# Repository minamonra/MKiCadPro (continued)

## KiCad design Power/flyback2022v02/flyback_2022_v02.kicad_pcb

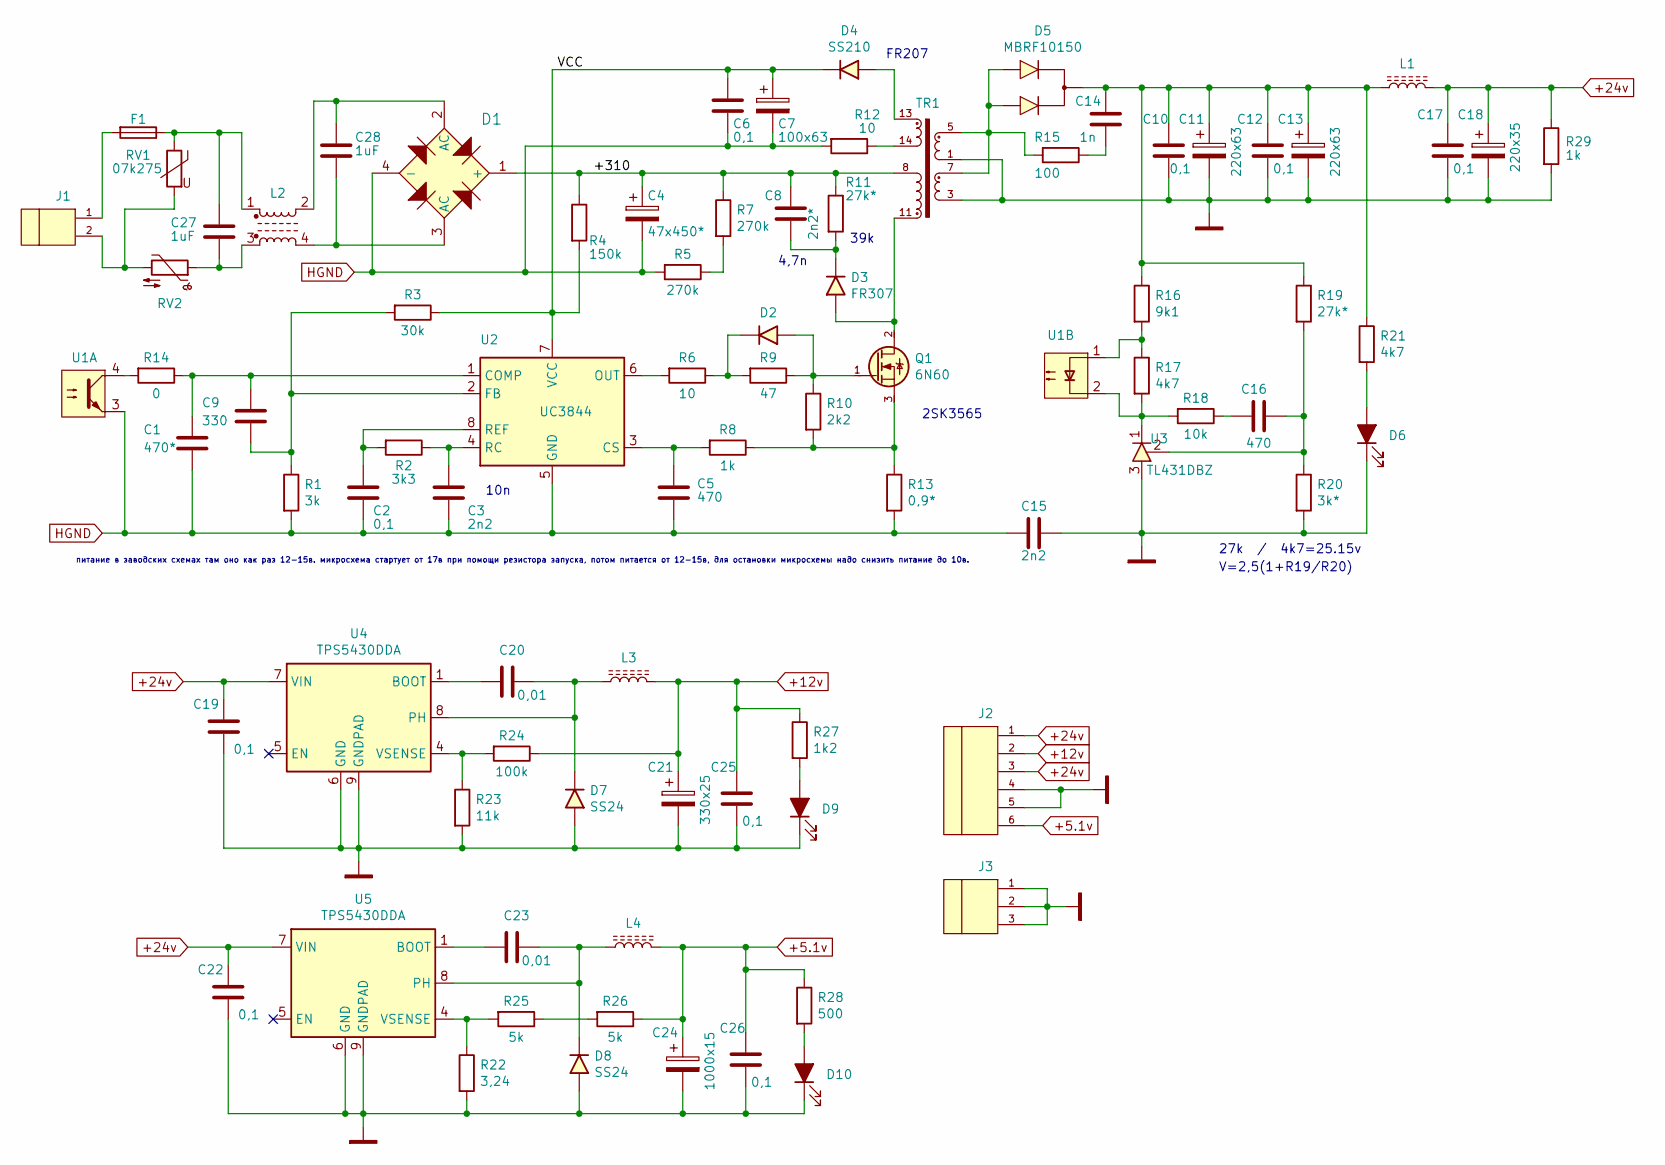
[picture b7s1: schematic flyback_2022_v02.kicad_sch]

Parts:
C1: 470*; capacitor_1206_3216Metric_V1
C2, C6, C10, C12, C17, C19, C22, C25, C26: 0,1; capacitor_1206_3216Metric_V1
C3: 2n2; capacitor_1206_3216Metric_V1
C4: 47x450*; CP_Radial_D17.0mm_P7.50mm
C5, C16: 470; capacitor_1206_3216Metric_V1
C7: 100x63; CP_D7.5_P2.5_zm0
C8: 2n2*; Capacitor_Y
C9: 330; capacitor_1206_3216Metric_V1
C11, C13: 220x63; CP_D10_P5.0_zm0
C14: 1n; capacitor_1206_3216Metric_V1
C15: 2n2; Capacitor_Y
C18: 220x35; CP_D10_P5.0_zm0
C20, C23: 0,01; capacitor_1206_3216Metric_V1
C21: 330x25; CP_D10_P5.0_zm0
C24: 1000x15; CP_D10_P5.0_zm0
C27, C28: 1uF; C_Rect_L10.0mm_W4.0mm_P7.50mm_MKS4
D1: KBP04G; Diode_bridge_RS207
D2: 4148; D_1206_3216Metric_Pad1.42x1.75mm_HandSolder
D3: FR307; D_DO-201AE_P5.08mm_Vertical_AnodeUp
D4: SS210; D_2010_5025Metric_SS14
D5: MBRF10150; HS_207_30_TO220
D6, D9, D10: LED_D3.0mm_zmod
D7, D8: SS24; D_2010_5025Metric_SS14
F1: 0,5; Fuseholder_BLX-A
J1: connector2p_v1; TerminalBlock_5_08_1
J2: connector6p; pin_1x06_P2.54mm_vertical
J3: connector3p; pin_1x03_P2.54mm_vertical
L1, L3, L4: L_Abracon_ASPI-0630LR
L2: Choke_Common_UU9LF
Q1: 6N60; HS_207_30_TO220
R1: 3k; resistor_1206_3216metric_V1
R2: 3k3; resistor_1206_3216metric_V1
R3: 30k; resistor_1206_3216metric_V1
R4: 150k; R_Axial_DIN0207_L6.3mm_D2.5mm_P10.16mm_Horizontal
R5, R7: 270k; resistor_1206_3216metric_V1
R6: 10; R_Axial_DIN0207_L6.3mm_D2.5mm_P10.16mm_Horizontal
R8: 1k; resistor_1206_3216metric_V1
R9: 47; resistor_1206_3216metric_V1
R10: 2k2; resistor_1206_3216metric_V1
R11: 27k*; R_Axial_DIN0614_L14.3mm_D5.7mm_P5.08mm_Vertical
R12: 10; resistor_1206_3216metric_V1
R13: 0,9*; R_Axial_DIN0207_L6.3mm_D2.5mm_P10.16mm_Horizontal
R14: 0; R_Axial_DIN0207_L6.3mm_D2.5mm_P10.16mm_Horizontal
R15: 100; R_Axial_DIN0614_L14.3mm_D5.7mm_P5.08mm_Vertical
R16: 9k1; resistor_1206_3216metric_V1
R17: 4k7; resistor_1206_3216metric_V1
R18: 10k; resistor_1206_3216metric_V1
R19: 27k*; resistor_1206_3216metric_V1
R20: 3k*; resistor_1206_3216metric_V1
R21: 4k7; R_Axial_DIN0207_L6.3mm_D2.5mm_P10.16mm_Horizontal
R22: 3,24; resistor_1206_3216metric_V1
R23: 11k; resistor_1206_3216metric_V1
R24: 100k; resistor_1206_3216metric_V1
R25, R26: 5k; resistor_1206_3216metric_V1
R27: 1k2; R_Axial_DIN0207_L6.3mm_D2.5mm_P10.16mm_Horizontal
R28: 500; resistor_1206_3216metric_V1
R29: 1k; R_Axial_DIN0614_L14.3mm_D5.7mm_P5.08mm_Vertical
RV1: 07k275; Capacitor_Y
RV2: 10; NTC_Thermistor_Epcos
TR1: Transformer_ETD29_1; Transformer_ETD-29_13_11_Horizontal
U1: PC817_AB; DIP-4_W7.62mm
U2: UC3844; DIP-8_W7.62mm_LongPads_3FLAT
U3: TL431DBZ; SOT-23
U4, U5: TPS5430DDA; TI_SO-PowerPAD-8_ThermalVias

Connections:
+5.1v: C24.1, C26.1, J2.6, L4.2, R26.1, R28.1
+12v: C21.1, C25.1, J2.2, L3.2, R24.1, R27.1
+24v: C17.1, C18.1, C19.1, C22.1, J2.1, J2.3, L1.2, R29.1, U4.7 (VIN), U5.7 (VIN)
/+310: C4.1, C8.1, D1.1 (+), R4.1, R7.1, R11.1, TR1.8
/VCC: C6.1, C7.1, D4.1 (K), R3.1, R4.2, U2.7 (VCC)
GND: C10.2, C11.2, C12.2, C13.2, C15.1, C17.2, C18.2, C19.2, C21.2, C22.2, C24.2, C25.2, C26.2, D6.1 (K), D7.2 (A), D8.2 (A), D9.1 (K), D10.1 (K), J2.4, J2.5, J3.1, J3.2, J3.3, R20.2, R22.2, R23.2, R29.2, TR1.1, TR1.3, U3.3 (A), U4.6 (GND), U4.9 (GNDPAD), U5.6 (GND), U5.9 (GNDPAD)
HGND: C1.2, C2.2, C3.2, C4.2, C5.2, C6.2, C7.2, C15.2, D1.4 (-), R1.2, R5.2, R12.2, R13.2, U1.3, U2.5 (GND)
unnamed: C1.1, C9.1, R14.1, U2.1 (COMP)
unnamed: C2.1, R2.2, U2.8 (REF)
unnamed: C3.1, R2.1, U2.4 (RC)
unnamed: C5.1, R8.2, U2.3 (CS)
unnamed: C8.2, D3.1 (K), R11.2
unnamed: C9.2, R1.1, R3.2, U2.2 (FB)
unnamed: C10.1, C11.1, C12.1, C13.1, C14.1, D5.2 (K), L1.1, R16.1, R19.1, R21.1
unnamed: C14.2, R15.1
unnamed: C16.1, R18.1
unnamed: C16.2, R19.2, R20.1, U3.2 (REF)
unnamed: C20.1, D7.1 (K), L3.1, U4.8 (PH)
unnamed: C20.2, U4.1 (BOOT)
unnamed: C23.1, D8.1 (K), L4.1, U5.8 (PH)
unnamed: C23.2, U5.1 (BOOT)
unnamed: C27.1, F1.1, L2.1, RV1.1
unnamed: C27.2, L2.3, RV2.1
unnamed: C28.1, D1.2 (AC), L2.2
unnamed: C28.2, D1.3 (AC), L2.4
unnamed: D2.1 (K), R6.1, R9.2
unnamed: D2.2 (A), Q1.1 (G), R9.1, R10.1
unnamed: D3.2 (A), Q1.2 (D), TR1.11
unnamed: D4.2 (A), TR1.13
unnamed: D5.1 (A), D5.3 (A), R15.2, TR1.5, TR1.7
unnamed: D6.2 (A), R21.2
unnamed: D9.2 (A), R27.2
unnamed: D10.2 (A), R28.2
unnamed: F1.2, J1.1
unnamed: J1.2, RV1.2, RV2.2
unnamed: Q1.3 (S), R8.1, R10.2, R13.1
unnamed: R5.1, R7.2
unnamed: R6.2, U2.6 (OUT)
unnamed: R12.1, TR1.14
unnamed: R14.2, U1.4
unnamed: R16.2, R17.1, U1.1
unnamed: R17.2, R18.2, U1.2, U3.1 (K)
unnamed: R22.1, R25.2, U5.4 (VSENSE)
unnamed: R23.1, R24.2, U4.4 (VSENSE)
unnamed: R25.1, R26.2

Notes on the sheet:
V=2,5(1+R19/R20)
39k
FR207
4,7n
питание в заводских схемах там оно как раз 12-15в. микросхема стартует от 17в при помощи резистора запуска, потом питается от 12-15в, для остановки микросхемы надо снизить питание до 10в.
27k / 4k7=25.15v
2SK3565
10n

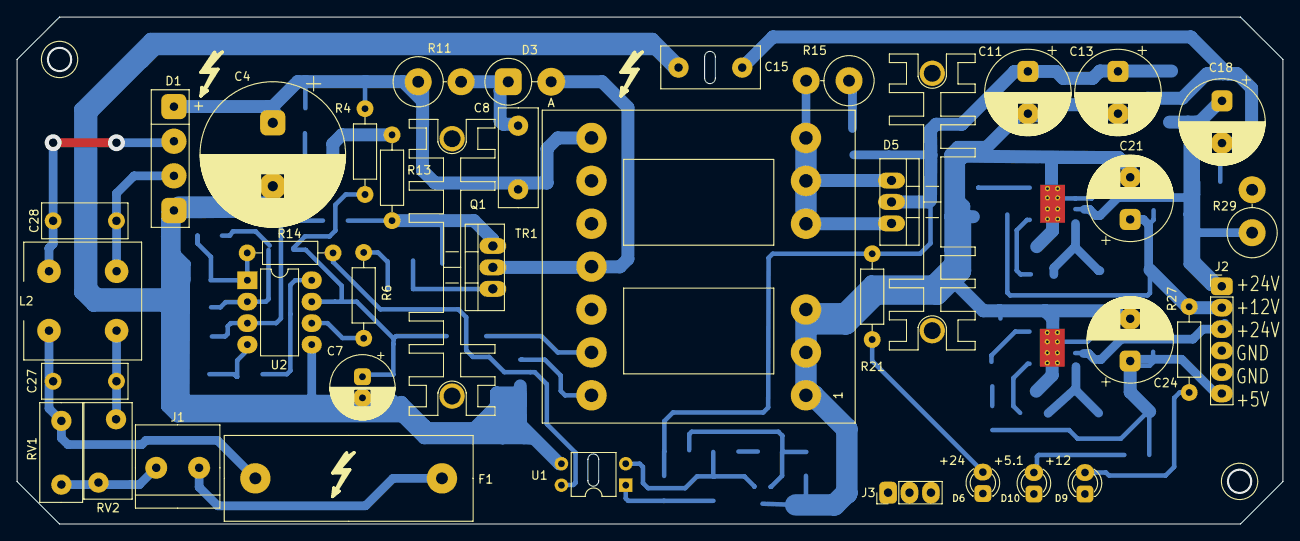
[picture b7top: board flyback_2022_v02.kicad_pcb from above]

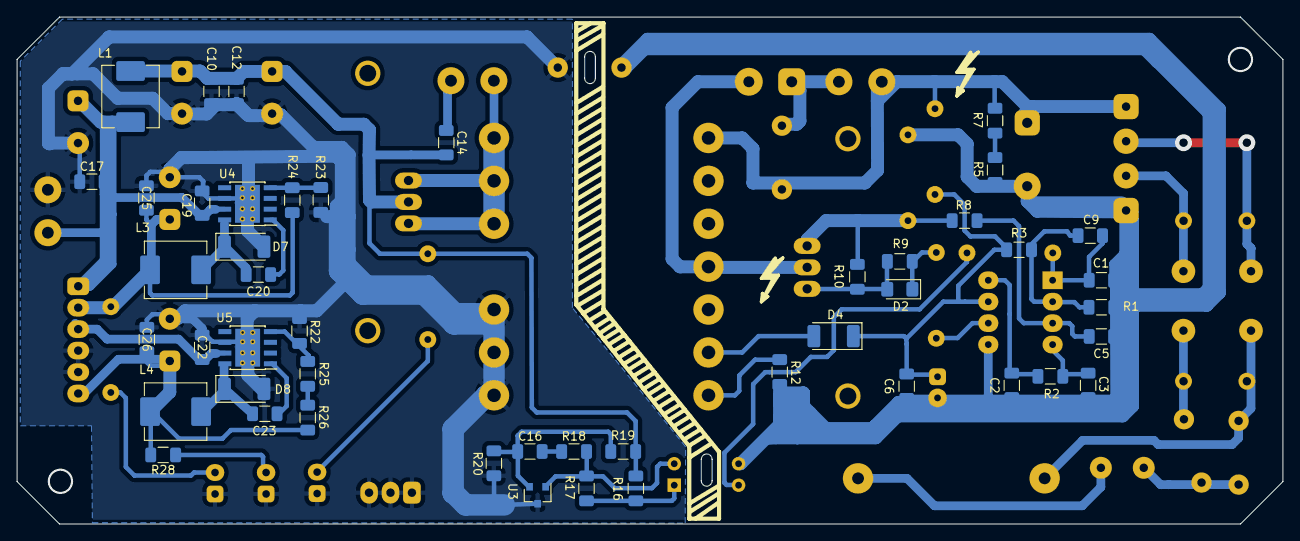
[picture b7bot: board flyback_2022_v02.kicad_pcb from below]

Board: 2 copper layers, 149.9 x 60.0 mm, 84 parts (47 on the bottom side), 45 nets.

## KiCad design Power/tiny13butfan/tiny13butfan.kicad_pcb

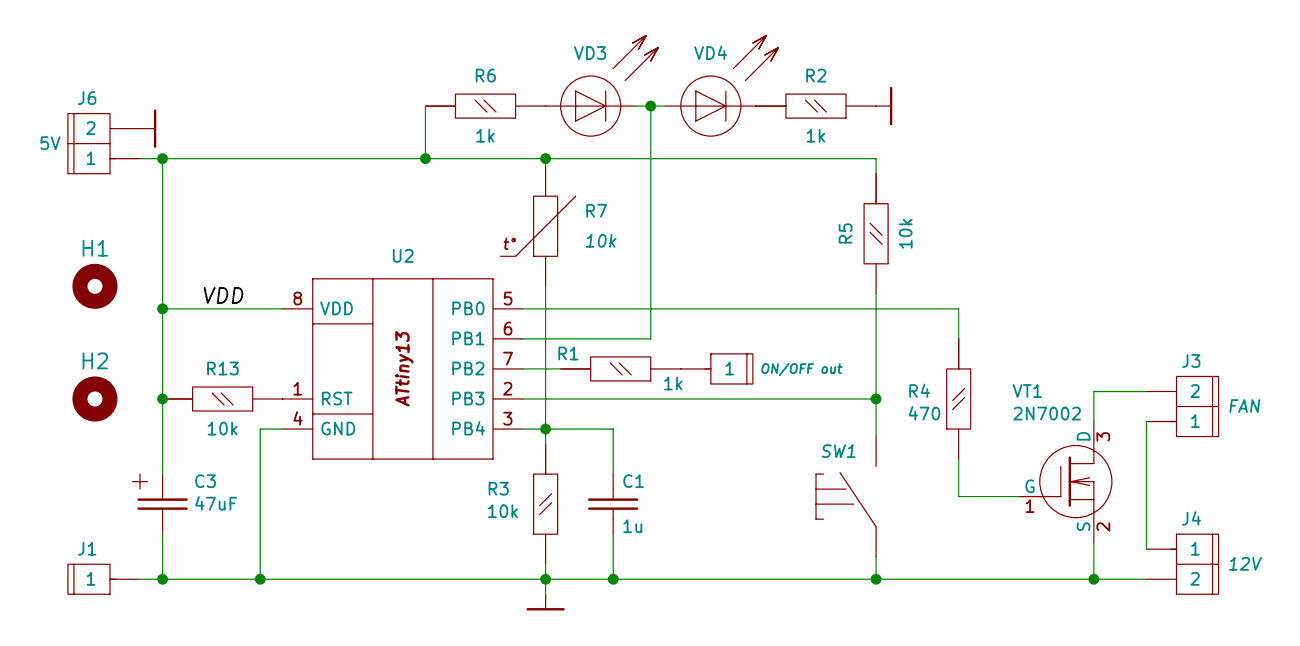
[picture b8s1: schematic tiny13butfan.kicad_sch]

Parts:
C1: 1u; C_1206_3216Metric
C3: 47uF; CP_EIA-3528-12_Kemet-T
H1, H2: MountingHole; MountingHole_3.2mm_M3
J1: CONN01PIN; SMD1PIN
J3: FAN; PinHeader_1x02_P2.54mm_Vertical
J4: 12V; PinHeader_1x02_P2.54mm_Vertical
J6: 5V; PinHeader_1x02_P2.54mm_Vertical
J8: ON/OFF out; PinHeader_1x01_P2.54mm_Vertical
R1, R2, R6: 1k; R_0805_2012Metric
R3, R5, R13: 10k; R_1206_3216Metric
R4: 470; R_1206_3216Metric
R7: 10k; switch_out
SW1: SWITCH1; PinHeader_1x02_P2.54mm_Vertical
U2: ATtiny13V-10S; DIP-8_W7.62mm_LongPads
VD3, VD4: LED; LED_1206_3216Metric_Pad1.42x1.75mm_HandSolder
VT1: 2N7002; SOT-23

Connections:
/VDD: C3.1, J6.1, R5.2, R6.2, R7.2, R13.2, U2.8 (VDD)
GND: C1.1, C3.2, J1.1, J4.2, J6.2, R2.1, R3.1, SW1.1, U2.4 (GND), VT1.2 (S)
unnamed: J3.1, J4.1
unnamed: J8.1, R1.1
unnamed: R4.2, U2.5 (PB0)
unnamed: U2.6 (PB1), VD3.1 (C), VD4.2 (A)
unnamed: R1.2, U2.7 (PB2)
unnamed: R5.1, SW1.2, U2.2 (PB3)
unnamed: C1.2, R3.2, R7.1, U2.3 (PB4)
unnamed: R13.1, U2.1 (RST)
unnamed: R6.1, VD3.2 (A)
unnamed: R2.2, VD4.1 (C)
unnamed: J3.2, VT1.3 (D)
unnamed: R4.1, VT1.1 (G)

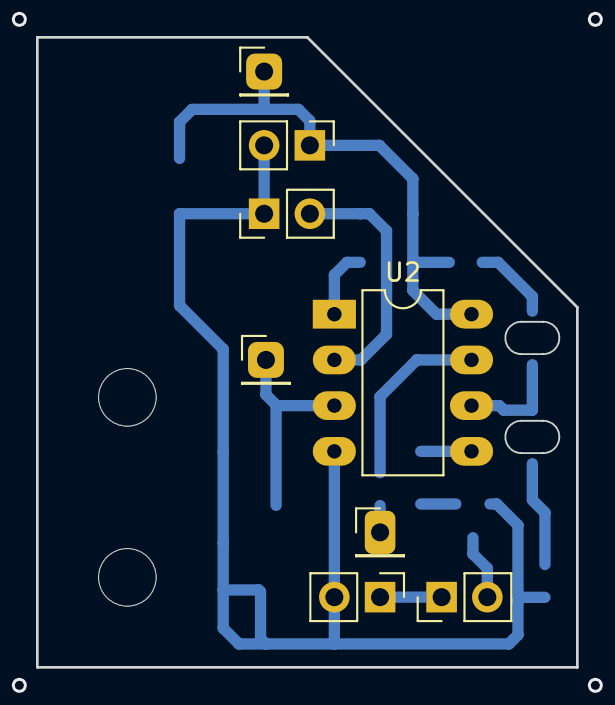
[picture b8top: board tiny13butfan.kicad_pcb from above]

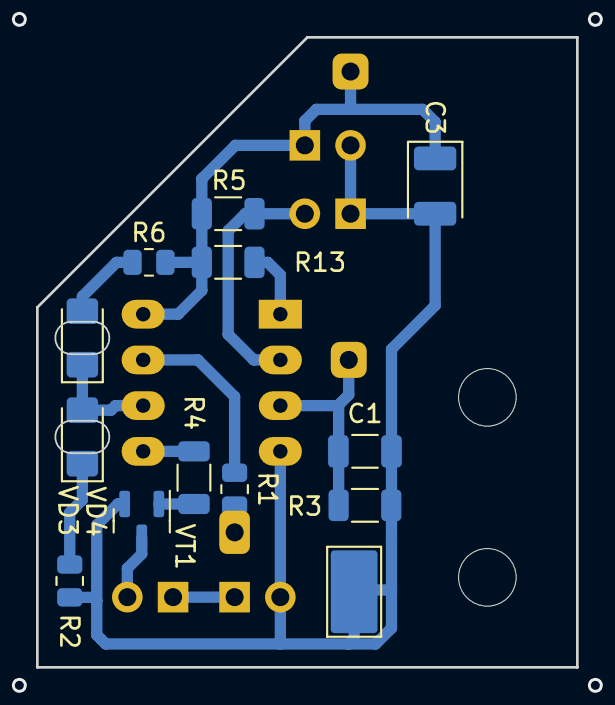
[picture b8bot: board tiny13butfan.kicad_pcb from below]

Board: 2 copper layers, 30.0 x 35.0 mm, 22 parts (13 on the bottom side), 14 nets.

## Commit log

2024-01-30 30.01up
2024-02-02 add tyn13butfan
2024-02-03 rename butoo fan
2024-02-03 up jpg
2024-02-04 Add flyback2022v02
2024-02-09 add kill_controll
2024-02-09 add pdf
2024-03-01 add old projects
2024-03-01 lora
2024-03-01 add sch
2024-08-26 August 2024
2024-08-27 R6. +24V, R1
2024-08-27 R15R16
2024-08-27 Add L1R20C7
2024-08-27 L1 betw R12&R15
2024-08-27 L1betwR12R15
2024-10-09 up oct 24
2025-03-30 fan_555_1st
